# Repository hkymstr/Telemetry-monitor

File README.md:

# Telemetry-monitor
telemetry monitor for raspberry pi pico

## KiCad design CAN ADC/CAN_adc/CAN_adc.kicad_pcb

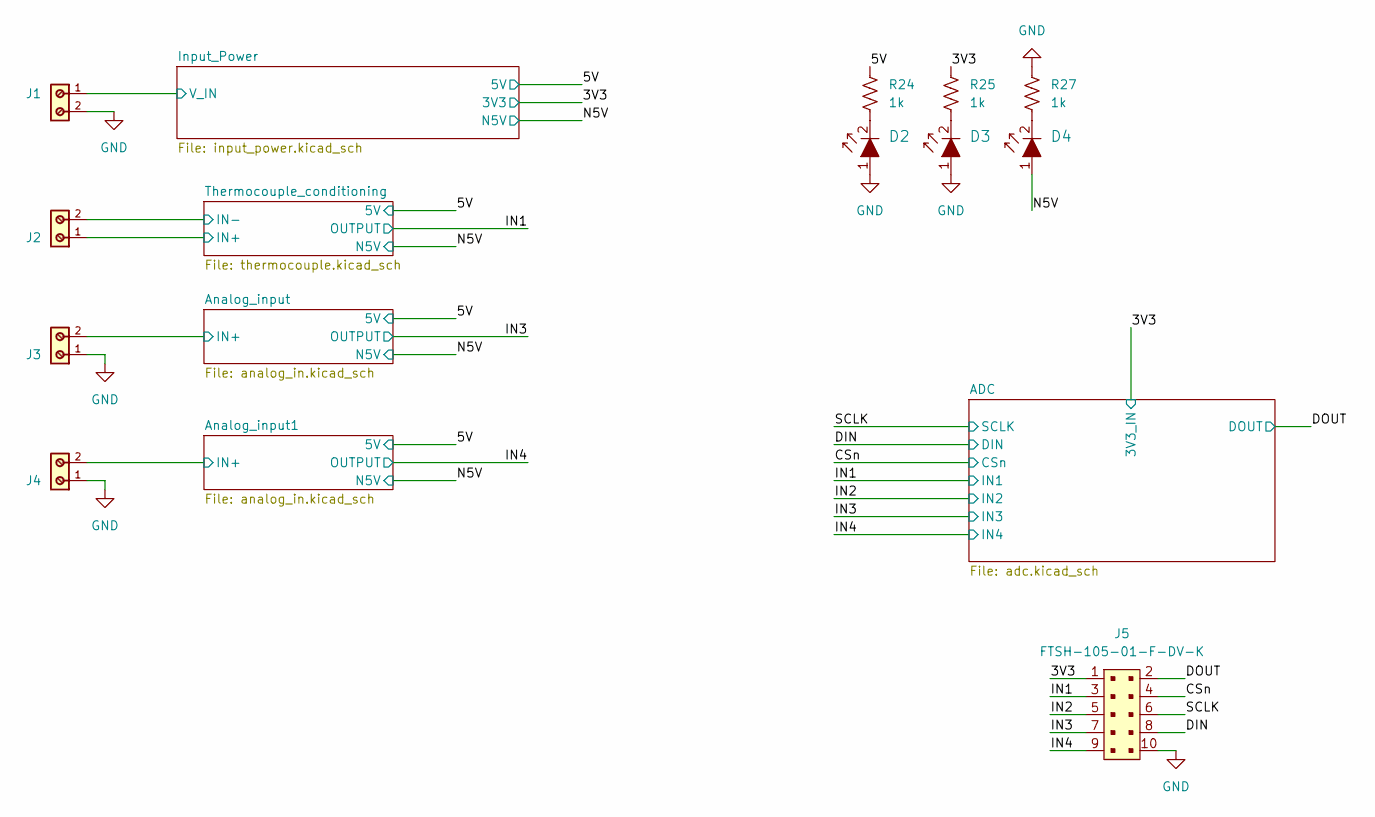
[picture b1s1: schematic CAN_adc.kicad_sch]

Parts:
D2, D3, D4: LG_L29K-G2J1-24-Z; 0603; MPN LG L29K-G2J1-24-Z; Digi-Key_PN 475-2709-1-ND
J1, J2, J3, J4: 691137710002; PART-NUMBER 691137710002
J5: FTSH-105-01-F-DV-K; PinHeader_2x5_P1.27_SMD; MPN FTSH-105-01-F-DV-K; Digi-Key_PN SAM8796-ND
R24, R25, R27: 1k; R_0603_1608Metric

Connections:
/3V3: J5.1, R25.1; also elsewhere on the board
/5V: R24.1; also elsewhere on the board
/Analog_input1/IN+: J4.2; also elsewhere on the board
/Analog_input/IN+: J3.2; also elsewhere on the board
/CSn: J5.4; also elsewhere on the board
/DIN: J5.8; also elsewhere on the board
/DOUT: J5.2; also elsewhere on the board
/IN1: J5.3; also elsewhere on the board
/IN2: J5.5; also elsewhere on the board
/IN3: J5.7; also elsewhere on the board
/IN4: J5.9; also elsewhere on the board
/Input_Power/V_IN: J1.1; also elsewhere on the board
/N5V: D4.1; also elsewhere on the board
/SCLK: J5.6; also elsewhere on the board
/Thermocouple_conditioning/IN+: J2.1; also elsewhere on the board
/Thermocouple_conditioning/IN-: J2.2; also elsewhere on the board
GND: D2.1, D3.1, J1.2, J3.1, J4.1, J5.10, R27.1; also elsewhere on the board
unnamed: D2.2, R24.2
unnamed: D3.2, R25.2
unnamed: D4.2, R27.2

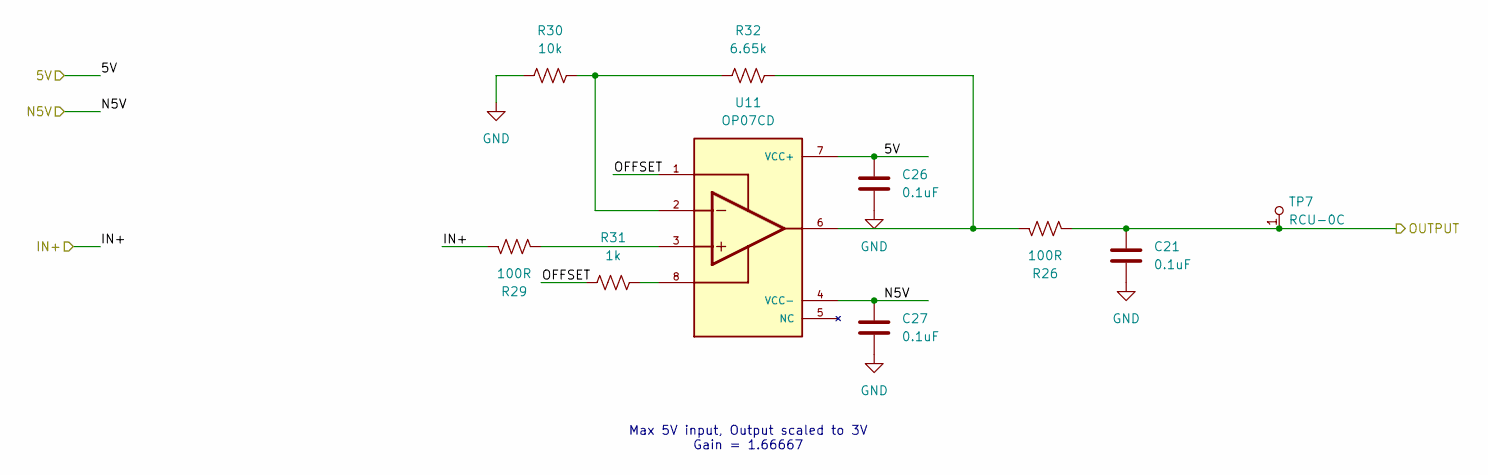
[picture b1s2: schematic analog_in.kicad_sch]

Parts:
C21, C26, C27: 0.1uF; C_0603_1608Metric_Pad1.08x0.95mm_HandSolder; Part Number CL10B104KB8NNNC
R26, R29: 100R; R_0603_1608Metric; Part Number RC0603FR-07100RL
R30: 10k; R_0603_1608Metric; Part Number RC0603FR-0710KL
R31: 1k; R_0603_1608Metric
R32: 6.65k; R_0603_1608Metric; Part Number RC0603FR-076K65L
TP7: RCU-0C; PROBE_PAD_0603; MPN RCU-0C; Digi-Key_PN A106145CT-ND
U11: OP07CD; SOIC127P599X175-8N

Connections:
/5V: C26.1, U11.7 (VCC+); also elsewhere on the board
/Analog_input/IN+: R29.1; also elsewhere on the board
/Analog_input/OFFSET: R31.1, U11.1
/IN3: C21.1, R26.2, TP7.1; also elsewhere on the board
/N5V: C27.1, U11.4 (VCC-); also elsewhere on the board
GND: C21.2, C26.2, C27.2, R30.1; also elsewhere on the board
unnamed: R26.1, R32.2, U11.6
unnamed: R29.2, U11.3
unnamed: R30.2, R32.1, U11.2
unnamed: R31.2, U11.8

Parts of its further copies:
C16, C17, C18: 0.1uF; C_0603_1608Metric_Pad1.08x0.95mm_HandSolder; Part Number CL10B104KB8NNNC
R19, R23: 100R; R_0603_1608Metric; Part Number RC0603FR-07100RL
R20: 10k; R_0603_1608Metric; Part Number RC0603FR-0710KL
R21: 1k; R_0603_1608Metric
R22: 6.65k; R_0603_1608Metric; Part Number RC0603FR-076K65L
TP6: RCU-0C; PROBE_PAD_0603; MPN RCU-0C; Digi-Key_PN A106145CT-ND
U7: OP07CD; SOIC127P599X175-8N

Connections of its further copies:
/5V: C16.1, U7.7 (VCC+); also elsewhere on the board
/Analog_input1/IN+: R19.1; also elsewhere on the board
/Analog_input1/OFFSET: R21.1, U7.1
/IN4: C18.1, R23.2, TP6.1; also elsewhere on the board
/N5V: C17.1, U7.4 (VCC-); also elsewhere on the board
GND: C16.2, C17.2, C18.2, R20.1; also elsewhere on the board
unnamed: R19.2, U7.3
unnamed: R20.2, R22.1, U7.2
unnamed: R21.2, U7.8
unnamed: R22.2, R23.1, U7.6

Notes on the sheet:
Max 5V input, Output scaled to 3V Gain = 1.66667

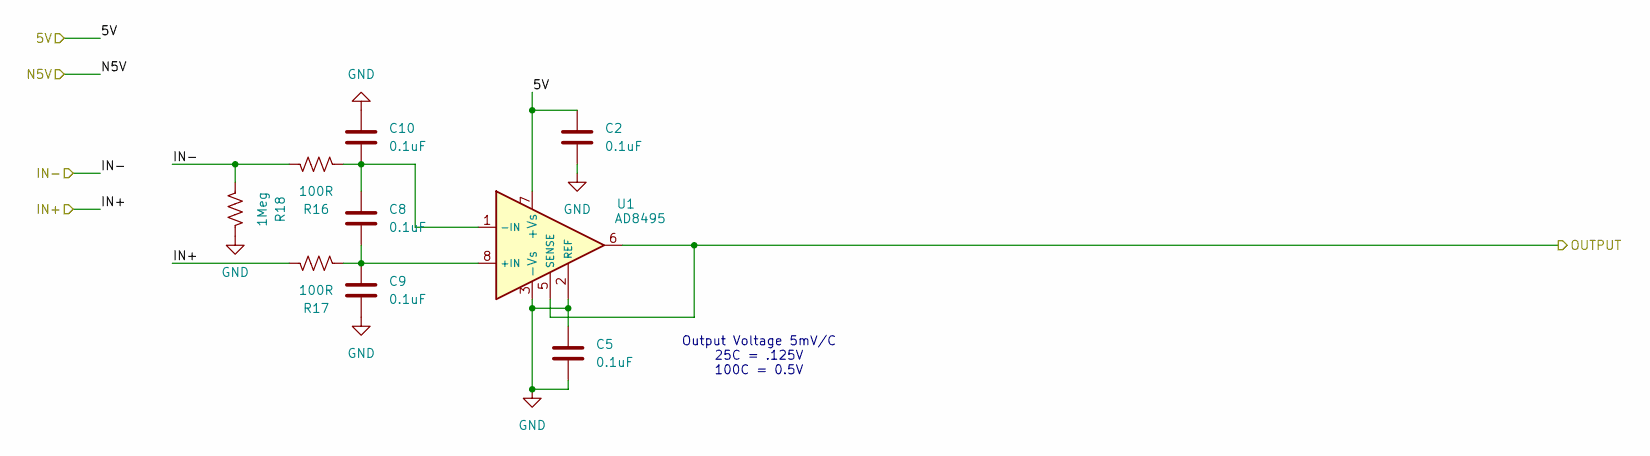
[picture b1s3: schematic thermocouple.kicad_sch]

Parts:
C2, C5, C8, C9, C10: 0.1uF; C_0603_1608Metric_Pad1.08x0.95mm_HandSolder; Part Number CL10B104KB8NNNC
R16, R17: 100R; R_0603_1608Metric; Part Number RC0603FR-07100RL
R18: 1Meg; R_0603_1608Metric; Part Number RC0603FR-071ML
U1: AD8495; MSOP-8_3x3mm_P0.65mm

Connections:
/5V: C2.1, U1.7 (+Vs); also elsewhere on the board
/IN1: U1.5 (SENSE), U1.6; also elsewhere on the board
/Thermocouple_conditioning/IN+: R17.1; also elsewhere on the board
/Thermocouple_conditioning/IN-: R16.1, R18.2; also elsewhere on the board
GND: C2.2, C5.1, C5.2, C9.2, C10.1, R18.1, U1.2 (REF), U1.3 (-Vs); also elsewhere on the board
unnamed: C8.2, C9.1, R17.2, U1.8 (+IN)
unnamed: C8.1, C10.2, R16.2, U1.1 (-IN)

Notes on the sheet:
Output Voltage 5mV/C 25C = .125V 100C = 0.5V

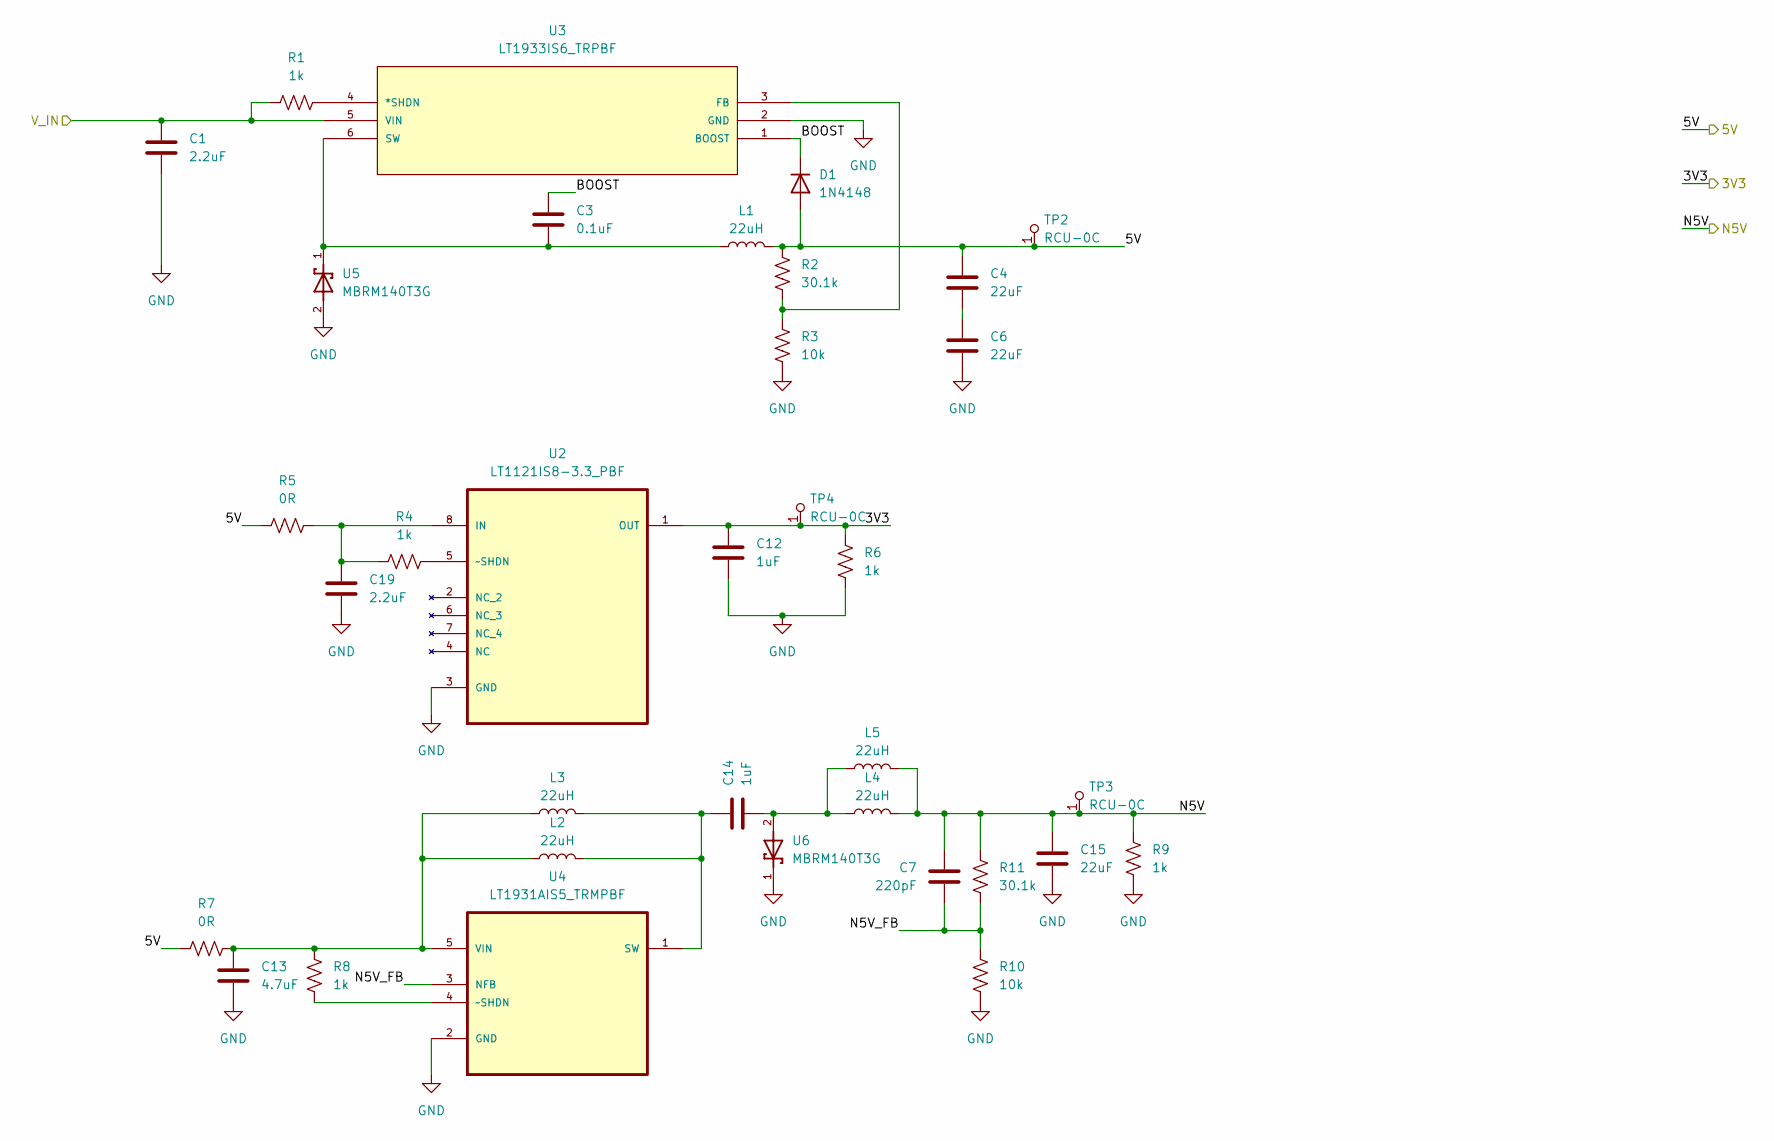
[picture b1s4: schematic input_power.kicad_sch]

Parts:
C1, C19: 2.2uF; C_1206_3216Metric; Part Number CL31B225KBHNNNE
C3: 0.1uF; C_0603_1608Metric_Pad1.08x0.95mm_HandSolder; Part Number CL10B104KB8NNNC
C4, C6, C15: 22uF; C_0805_2012Metric_Pad1.18x1.45mm_HandSolder; Part Number CL21A226MAYNNNE
C7: 220pF; C_0603_1608Metric_Pad1.08x0.95mm_HandSolder; Part Number 0603B221K500CT
C12, C14: 1uF; C_0603_1608Metric_Pad1.08x0.95mm_HandSolder; Part Number CL10B105KA8NNNC
C13: 4.7uF; C_1206_3216Metric_Pad1.33x1.80mm_HandSolder; Part Number CL31B475KBHNFNE
D1: 1N4148; D_SOD-523; Part Number 1N4148WT
L1, L2, L3, L4, L5: 22uH; L_1210_3225Metric_Pad1.42x2.65mm_HandSolder; Part Number CBC3225T220KR
R1, R4, R6, R8, R9: 1k; R_0603_1608Metric
R2, R11: 30.1k; R_0603_1608Metric; Part Number RMCF0603FT30K1
R3, R10: 10k; R_0603_1608Metric; Part Number RC0603FR-0710KL
R5, R7: 0R; R_0603_1608Metric
TP2, TP3, TP4: RCU-0C; PROBE_PAD_0603; MPN RCU-0C; Digi-Key_PN A106145CT-ND
U2: LT1121IS8-3.3_PBF; SOIC127P600X175-8N; MPN LT1121IS8#PBF
U3: LT1933IS6_TRPBF; TSOT-23_S6; MANUFACTURER_PART_NUMBER lt1933is6
U4: LT1931AIS5_TRMPBF; SOT95P280X100-5N; MPN LT1931ES5#PBF
U5, U6: MBRM140T3G; DIO_MBRM110LT1G

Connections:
/3V3: C12.1, R6.1, TP4.1, U2.1 (OUT); also elsewhere on the board
/5V: C4.1, D1.2 (A), L1.2, R2.1, R5.1, R7.1, TP2.1; also elsewhere on the board
/Input_Power/BOOST: C3.1, D1.1 (K), U3.1 (BOOST)
/Input_Power/N5V_FB: C7.2, R10.1, R11.2, U4.3 (NFB)
/Input_Power/V_IN: C1.1, R1.2, U3.5 (VIN); also elsewhere on the board
/N5V: C7.1, C15.1, L4.2, L5.2, R9.1, R11.1, TP3.1; also elsewhere on the board
GND: C1.2, C6.2, C12.2, C13.2, C15.2, C19.2, R3.2, R6.2, R9.2, R10.2, U2.3 (GND), U3.2 (GND), U4.2 (GND), U5.2, U6.1; also elsewhere on the board
unnamed: C4.2, C6.1
unnamed: C14.2, L4.1, L5.1, U6.2
unnamed: C19.1, R4.2, R5.2, U2.8 (IN)
unnamed: R4.1, U2.5 (~SHDN)
unnamed: R1.1, U3.4 (*SHDN)
unnamed: R2.2, R3.1, U3.3 (FB)
unnamed: C3.2, L1.1, U3.6 (SW), U5.1
unnamed: C14.1, L2.2, L3.2, U4.1 (SW)
unnamed: C13.1, L2.1, L3.1, R7.2, R8.1, U4.5 (VIN)
unnamed: R8.2, U4.4 (~SHDN)

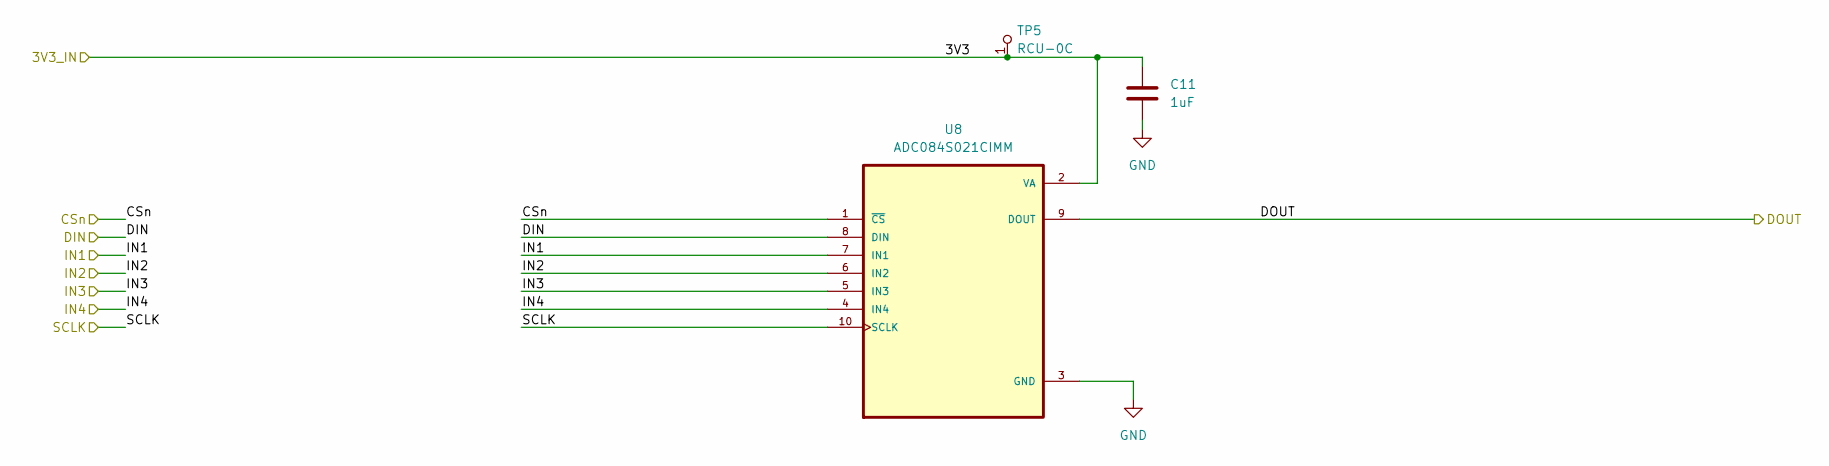
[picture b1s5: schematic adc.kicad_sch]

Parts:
C11: 1uF; C_0603_1608Metric_Pad1.08x0.95mm_HandSolder; Part Number CL10B105KA8NNNC
TP5: RCU-0C; PROBE_PAD_0603; MPN RCU-0C; Digi-Key_PN A106145CT-ND
U8: ADC084S021CIMM; SOP50P490X110-10N

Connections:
/3V3: C11.1, TP5.1, U8.2 (VA); also elsewhere on the board
/CSn: U8.1 (~CS); also elsewhere on the board
/DIN: U8.8 (DIN); also elsewhere on the board
/DOUT: U8.9 (DOUT); also elsewhere on the board
/IN1: U8.7 (IN1); also elsewhere on the board
/IN2: U8.6 (IN2); also elsewhere on the board
/IN3: U8.5 (IN3); also elsewhere on the board
/IN4: U8.4 (IN4); also elsewhere on the board
/SCLK: U8.10 (SCLK); also elsewhere on the board
GND: C11.2, U8.3 (GND); also elsewhere on the board

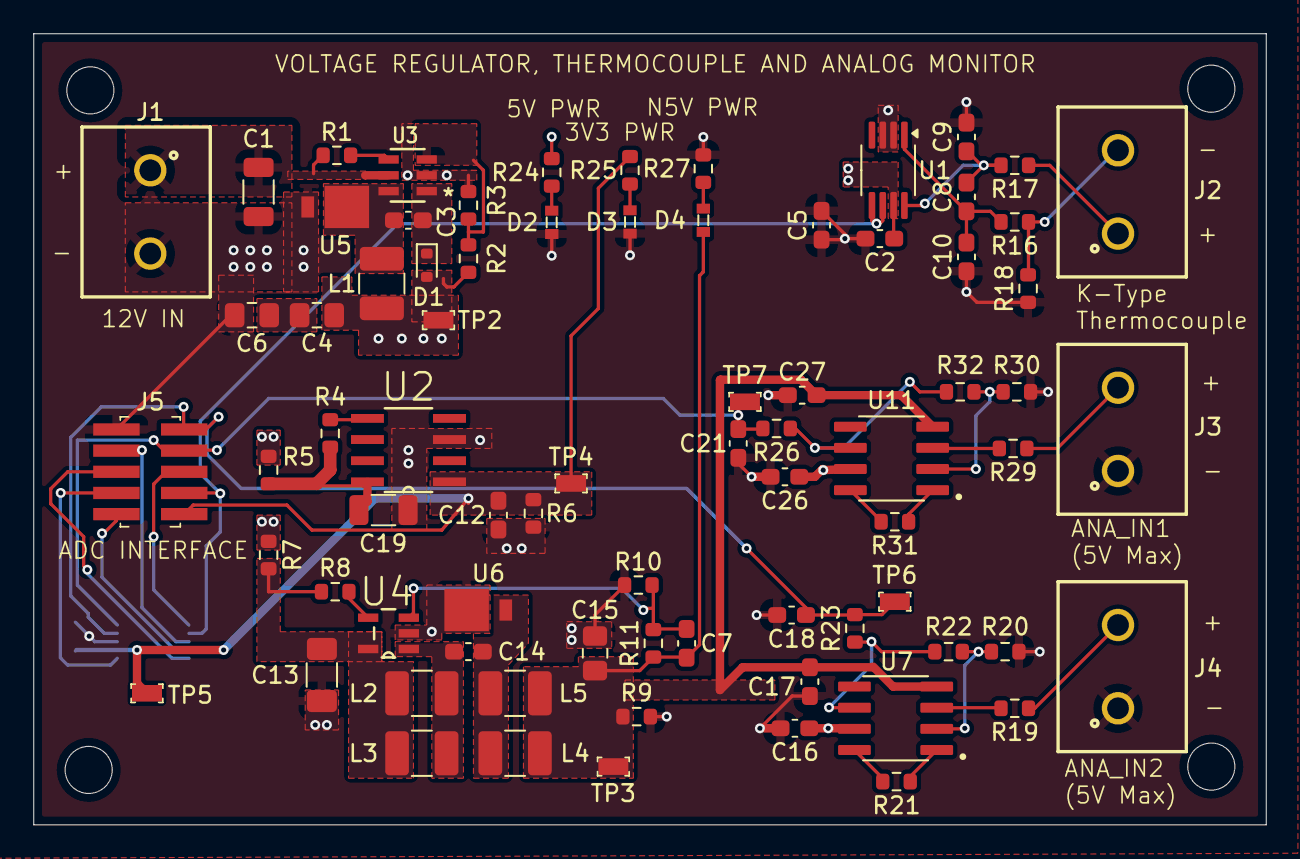
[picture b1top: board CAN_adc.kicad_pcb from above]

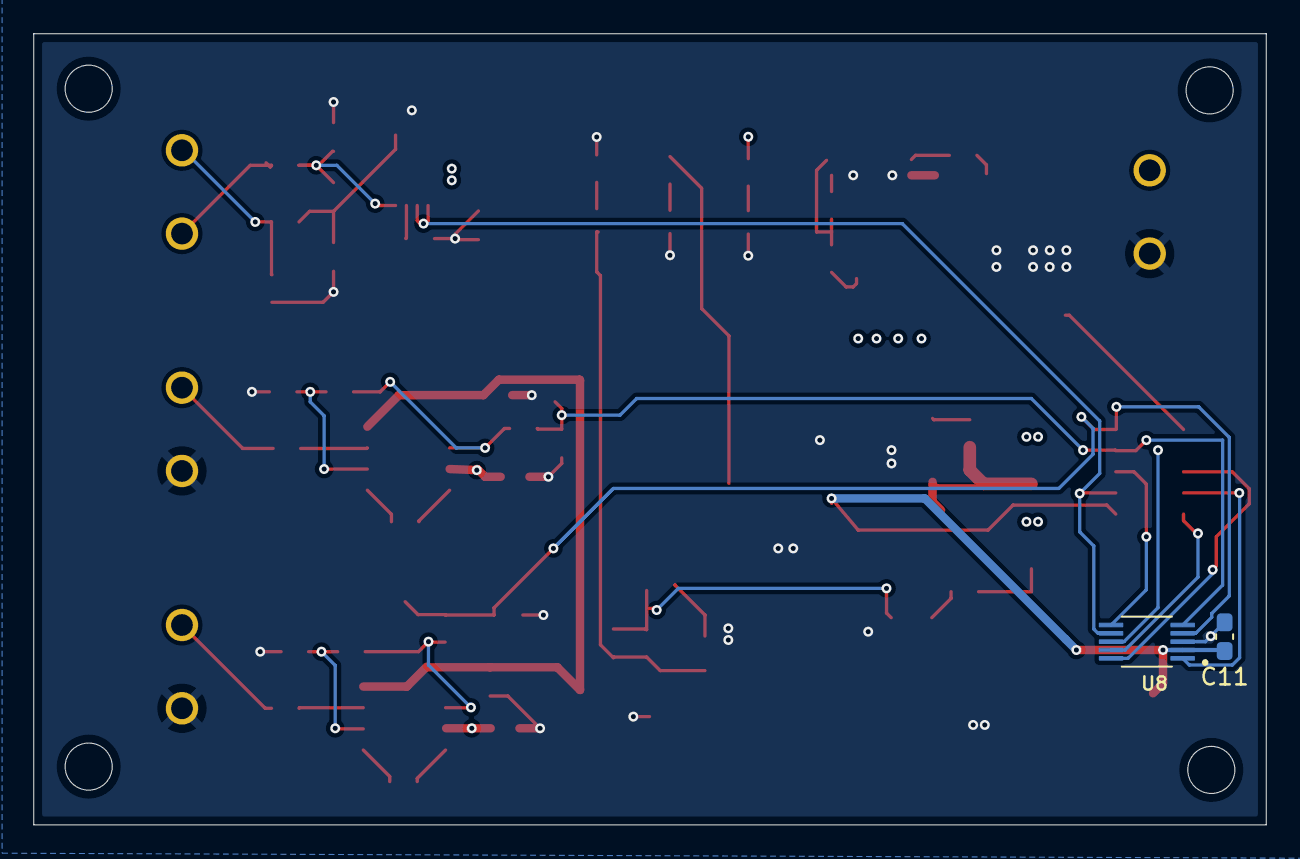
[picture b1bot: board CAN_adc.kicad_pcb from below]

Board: 4 copper layers, 74.0 x 47.5 mm, 78 parts (2 on the bottom side), 44 nets.

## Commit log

2024-12-15 Add files via upload
    file to read ADC via SPI
2024-12-15 Add files via upload
    KiCAD files
2024-12-15 Update code.py
    updated code using ChatGPT
2024-12-15 Update code.py
    updated to add sleep between reads
2024-12-25 Update code.py
    Updated code to correctly address ADC. Not getting correct ADC channels reads back
2024-12-25 Update code.py
    revised code, still not get consistent channel 2 and 3 reads, they seem to switch
2024-12-27 Create telem_arduino_uno_r3
    Code revision for Arduino Uno R3 with CAN board to log data on SDcard.
2024-12-27 Create code_rp2040_external_internal_ADC.py
    code for an RP2040 pico to read external ADC (8-bit) and internal ADC (12-bit) plus temperature monitoring
2024-12-27 Update telem_arduino_uno_r3
    updated ADC channels for external ADC
2024-12-27 Update telem_arduino_uno_r3
    Edited code for Arduino to account for pipelined ADC reads. The current channel selected is the previous channel readout.
2024-12-27 Update code_rp2040_external_internal_ADC.py
    revised code for pipelined ADC reads
2024-12-27 Update code_rp2040_external_internal_ADC.py
    minor updates to scan all external channels
2024-12-27 Update code_rp2040_external_internal_ADC.py
    this code fixes the pipelining of the ADCs.
2024-12-27 Create rp2040_adc084s021
    This code will read the ADC084S021 correct, however this needs to implement pipe-lining to read the correct channels.
2024-12-27 Update rp2040_adc084s021
    fixed pipelining and added voltage conversion
2024-12-29 Update code_rp2040_external_internal_ADC.py
    Revised this code to read external ADC in pipelined fashion. Also maintain internal ADC measurements and conversions.
2024-12-29 Create rp2040_ADC_micropython
    Micropython version of rp2040 code
